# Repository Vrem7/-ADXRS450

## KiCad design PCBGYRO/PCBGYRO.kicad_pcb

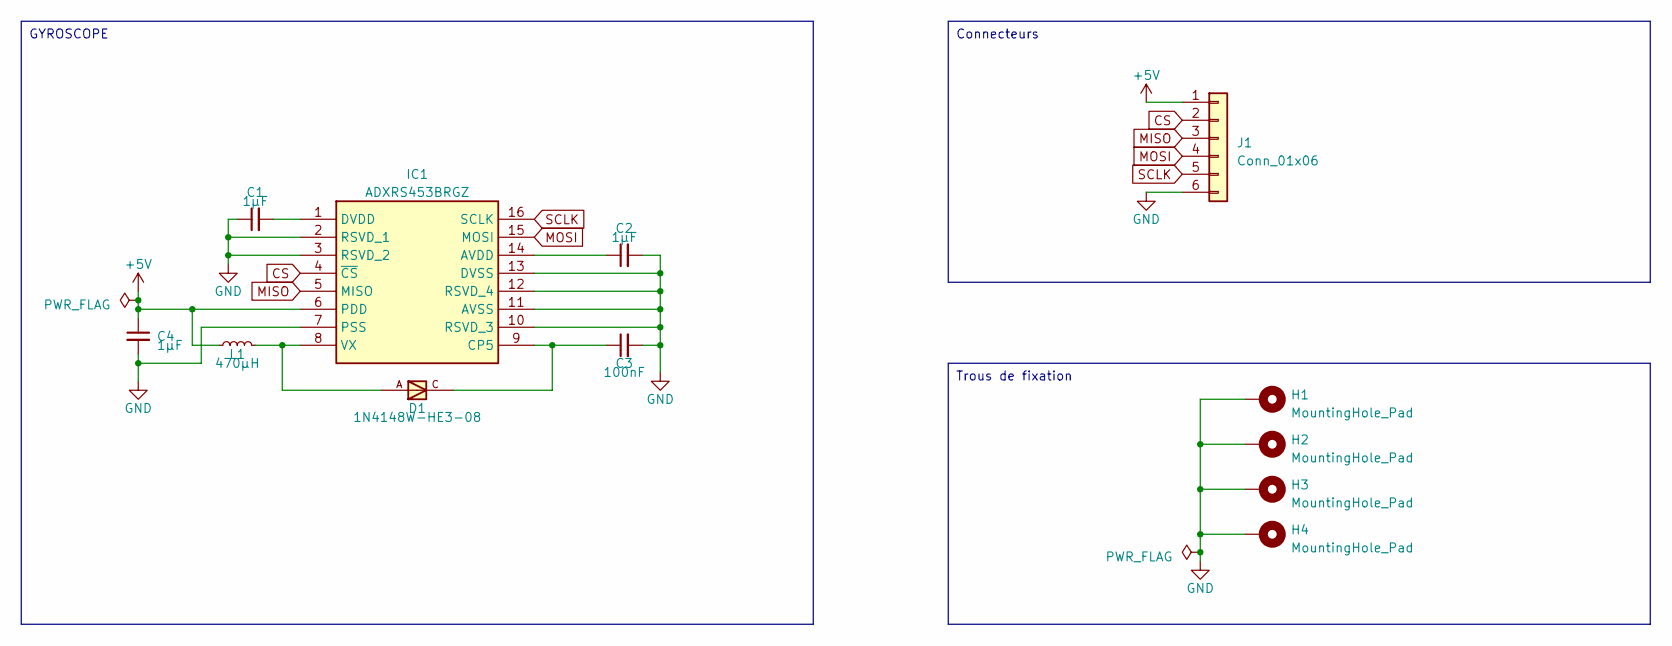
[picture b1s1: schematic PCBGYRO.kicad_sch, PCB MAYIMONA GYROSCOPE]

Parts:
C1, C2, C4: 1µF; C_0603_1608Metric_Pad1.08x0.95mm_HandSolder
C3: 100nF; C_0603_1608Metric_Pad1.08x0.95mm_HandSolder
D1: 1N4148W-HE3-08; SOD3715X135N; PARTREV 1.7
H1, H2, H3, H4: MountingHole_Pad; MountingHole_3.2mm_M3_DIN965_Pad
IC1: ADXRS453BRGZ; SOIC127P1042X373-16N; Mouser Part Number 584-ADXRS453BRGZ
J1: Conn_01x06; JST_XH_B6B-XH-A_1x06_P2.50mm_Vertical
L1: 470µH; CAP_GRM43N5C2H102KYXHL

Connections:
+5V: C4.1, IC1.6 (PDD), J1.1, L1.1
CS: IC1.4 (~CS), J1.2
GND: C1.1, C2.2, C3.2, C4.2, H1.1, H2.1, H3.1, H4.1, IC1.2 (RSVD_1), IC1.3 (RSVD_2), IC1.7 (PSS), IC1.10 (RSVD_3), IC1.11 (AVSS), IC1.12 (RSVD_4), IC1.13 (DVSS), J1.6
MISO: IC1.5 (MISO), J1.3
MOSI: IC1.15 (MOSI), J1.4
unnamed: C2.1, IC1.14 (AVDD)
unnamed: C3.1, D1.C, IC1.9 (CP5)
unnamed: C1.2, IC1.1 (DVDD)
unnamed: D1.A, IC1.8 (VX), L1.2
SCLK: IC1.16 (SCLK), J1.5

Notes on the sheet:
Trous de fixation
GYROSCOPE
Connecteurs

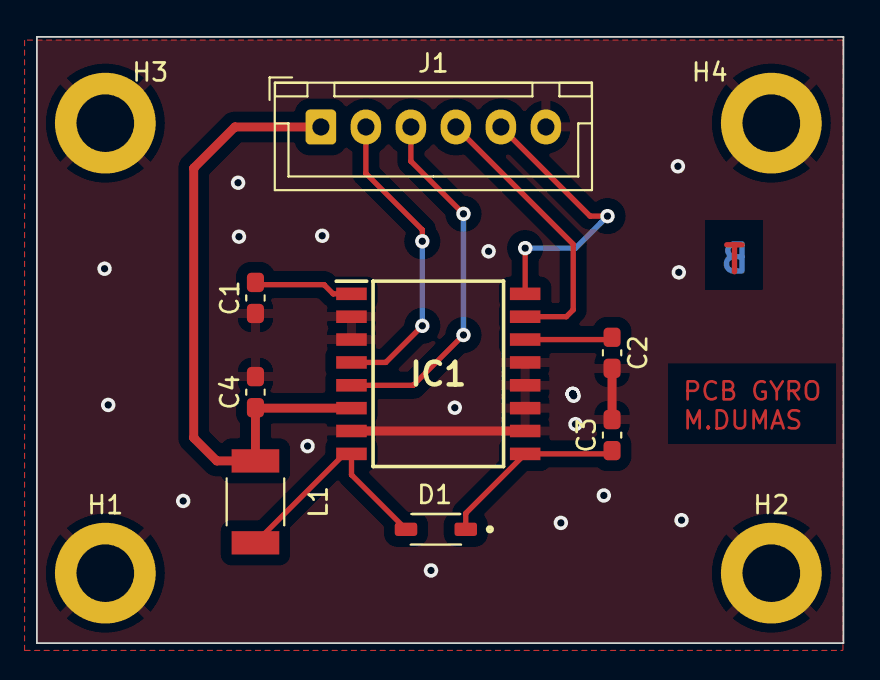
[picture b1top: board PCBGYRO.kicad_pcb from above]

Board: 2 copper layers, 44.8 x 33.7 mm, 12 parts (0 on the bottom side), 10 nets.
